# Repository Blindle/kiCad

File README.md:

# kiCad
electronic circuit - schema

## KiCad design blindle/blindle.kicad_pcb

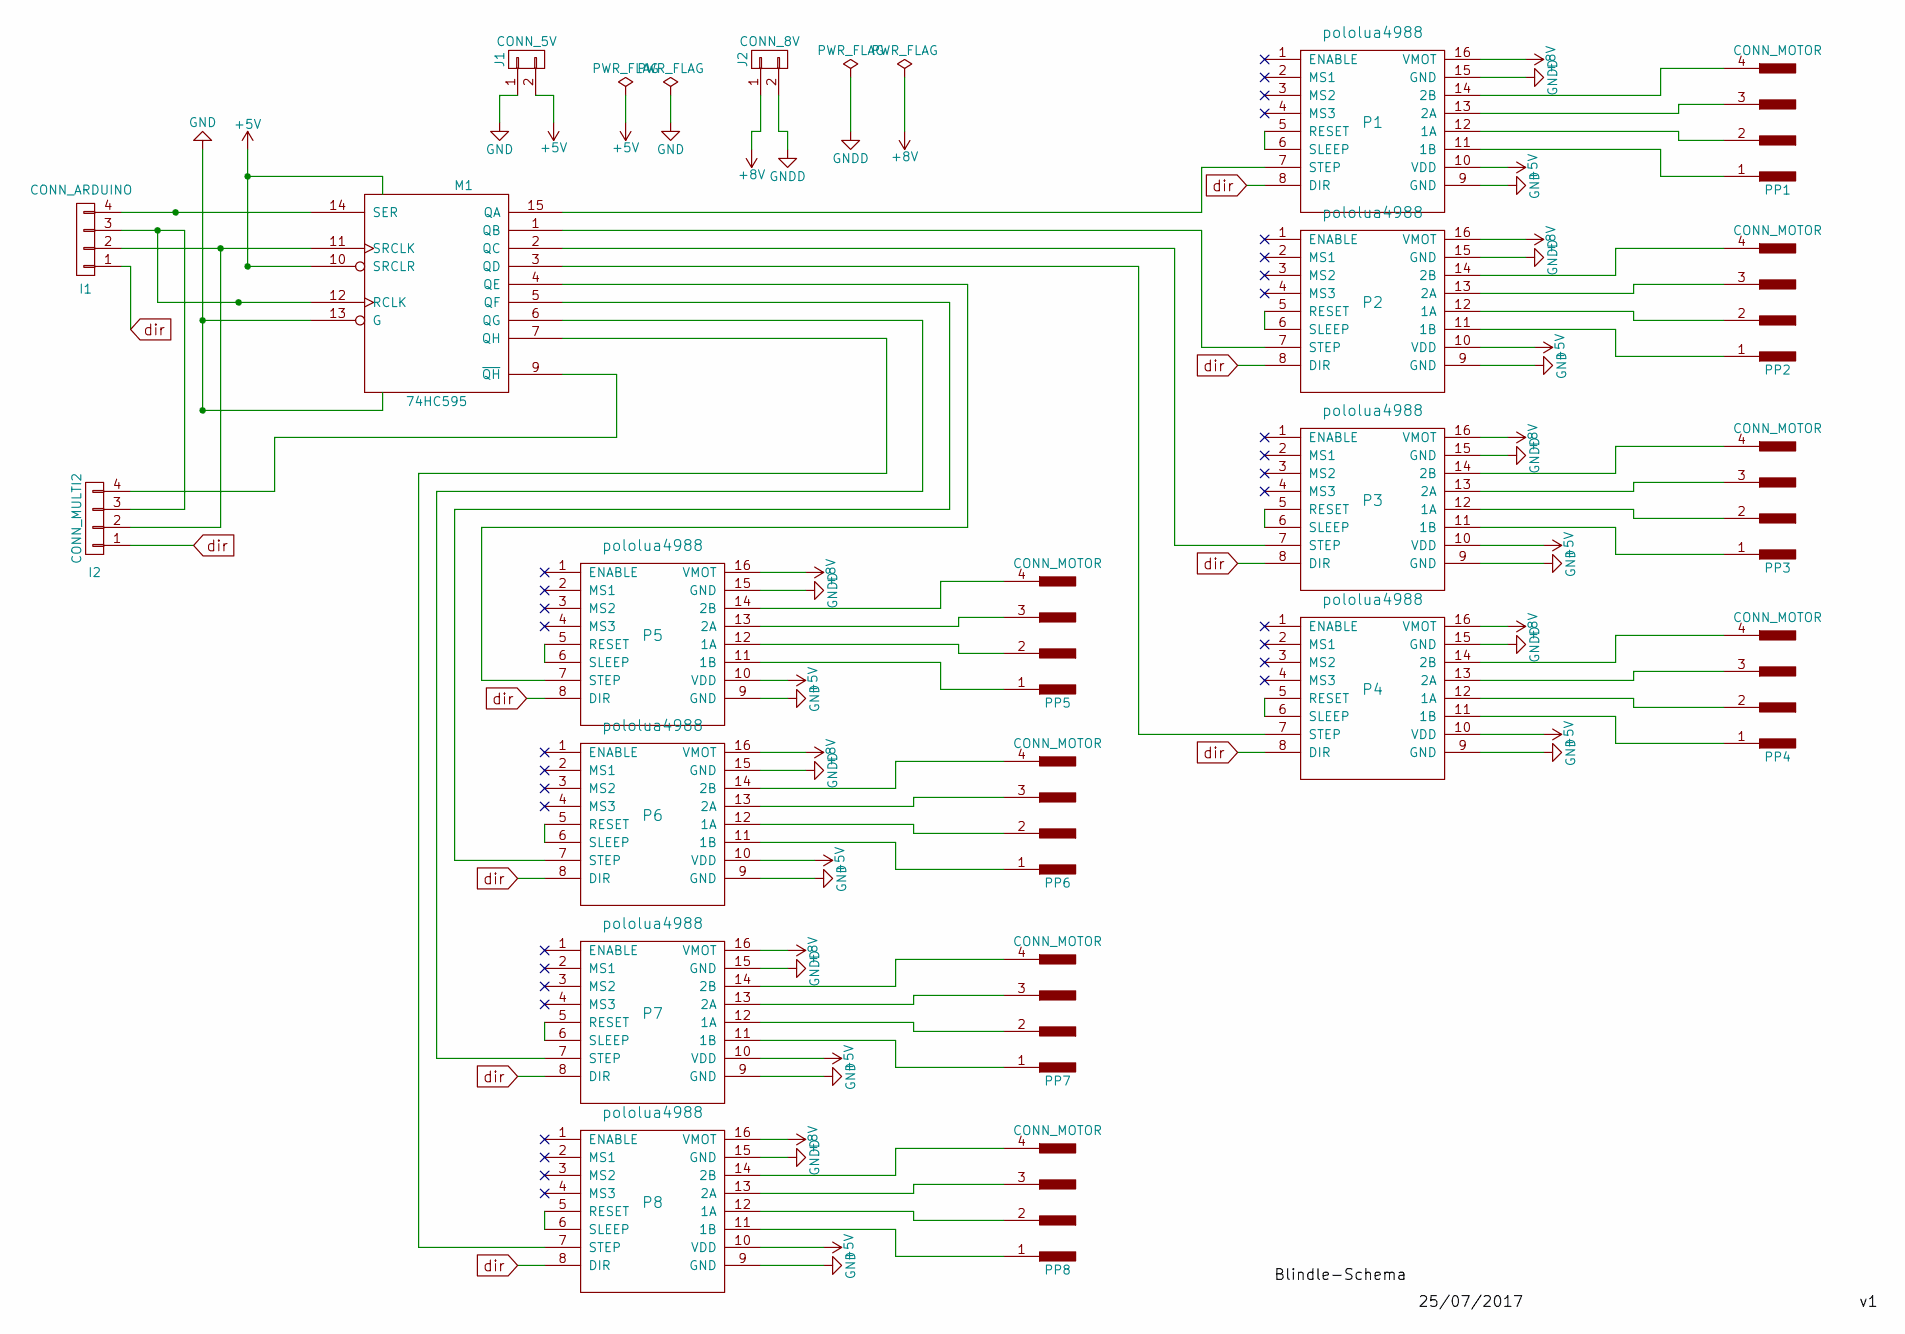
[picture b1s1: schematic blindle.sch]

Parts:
I1: CONN_ARDUINO; Pin_Header_Straight_1x04_Pitch2.54mm
I2: CONN_MULTI2; Pin_Header_Straight_1x04_Pitch2.54mm
J1: CONN_5V; PINHEAD1-2
J2: CONN_8V; bornier2
M1: 74HC595; DIP-16_W7.62mm_LongPads
P1, P2, P3, P4, P5, P6, P7, P8: pololua4988
PP1, PP2, PP3, PP4, PP5, PP6, PP7, PP8: CONN_MOTOR; Pin_Header_Straight_1x04_Pitch2.54mm

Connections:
+5V: J1.2, M1.10 (SRCLR), M1.16 (VCC), P1.10 (VDD), P2.10 (VDD), P3.10 (VDD), P4.10 (VDD), P5.10 (VDD), P6.10 (VDD), P7.10 (VDD), P8.10 (VDD)
+8V: J2.1, P1.16 (VMOT), P2.16 (VMOT), P3.16 (VMOT), P4.16 (VMOT), P5.16 (VMOT), P6.16 (VMOT), P7.16 (VMOT), P8.16 (VMOT)
GND: J1.1, M1.8 (GND), M1.13 (G), P1.9 (GND), P2.9 (GND), P3.9 (GND), P4.9 (GND), P5.9 (GND), P6.9 (GND), P7.9 (GND), P8.9 (GND)
GNDD: J2.2, P1.15 (GND), P2.15 (GND), P3.15 (GND), P4.15 (GND), P5.15 (GND), P6.15 (GND), P7.15 (GND), P8.15 (GND)
unnamed: I1.2, I2.2, M1.11 (SRCLK)
unnamed: I1.3, I2.3, M1.12 (RCLK)
unnamed: I1.4, M1.14 (SER)
unnamed: I2.4, M1.9 (~QH)
unnamed: M1.1 (QB), P2.7 (STEP)
unnamed: M1.2 (QC), P3.7 (STEP)
unnamed: M1.3 (QD), P4.7 (STEP)
unnamed: M1.4 (QE), P5.7 (STEP)
unnamed: M1.5 (QF), P6.7 (STEP)
unnamed: M1.6 (QG), P7.7 (STEP)
unnamed: M1.7 (QH), P8.7 (STEP)
unnamed: M1.15 (QA), P1.7 (STEP)
unnamed: P1.5 (RESET), P1.6 (SLEEP)
unnamed: P1.11 (1B), PP1.1
unnamed: P1.12 (1A), PP1.2
unnamed: P1.13 (2A), PP1.3
unnamed: P1.14 (2B), PP1.4
unnamed: P2.5 (RESET), P2.6 (SLEEP)
unnamed: P2.11 (1B), PP2.1
unnamed: P2.12 (1A), PP2.2
unnamed: P2.13 (2A), PP2.3
unnamed: P2.14 (2B), PP2.4
unnamed: P3.5 (RESET), P3.6 (SLEEP)
unnamed: P3.11 (1B), PP3.1
unnamed: P3.12 (1A), PP3.2
unnamed: P3.13 (2A), PP3.3
unnamed: P3.14 (2B), PP3.4
unnamed: P4.5 (RESET), P4.6 (SLEEP)
unnamed: P4.11 (1B), PP4.1
unnamed: P4.12 (1A), PP4.2
unnamed: P4.13 (2A), PP4.3
unnamed: P4.14 (2B), PP4.4
unnamed: P5.5 (RESET), P5.6 (SLEEP)
unnamed: P5.11 (1B), PP5.1
unnamed: P5.12 (1A), PP5.2
unnamed: P5.13 (2A), PP5.3
unnamed: P5.14 (2B), PP5.4
unnamed: P6.5 (RESET), P6.6 (SLEEP)
unnamed: P6.11 (1B), PP6.1
unnamed: P6.12 (1A), PP6.2
unnamed: P6.13 (2A), PP6.3
unnamed: P6.14 (2B), PP6.4
unnamed: P7.5 (RESET), P7.6 (SLEEP)
unnamed: P7.11 (1B), PP7.1
unnamed: P7.12 (1A), PP7.2
unnamed: P7.13 (2A), PP7.3
unnamed: P7.14 (2B), PP7.4
unnamed: P8.5 (RESET), P8.6 (SLEEP)
unnamed: P8.11 (1B), PP8.1
unnamed: P8.12 (1A), PP8.2
unnamed: P8.13 (2A), PP8.3
unnamed: P8.14 (2B), PP8.4
dir: I1.1, I2.1, P1.8 (DIR), P2.8 (DIR), P3.8 (DIR), P4.8 (DIR), P5.8 (DIR), P6.8 (DIR), P7.8 (DIR), P8.8 (DIR)

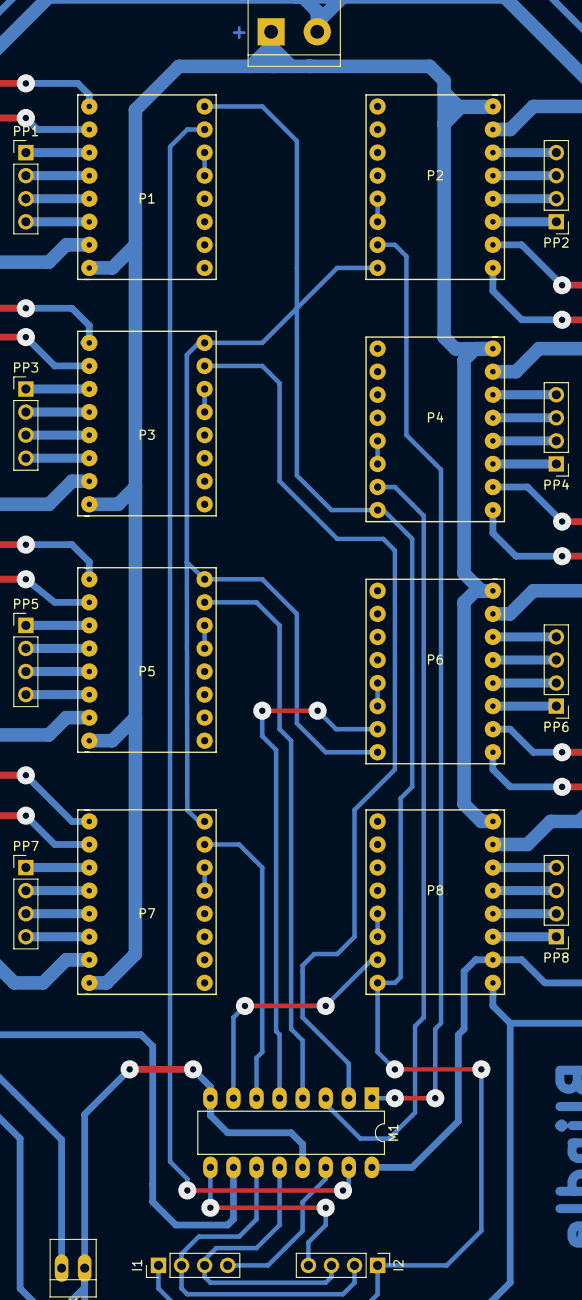
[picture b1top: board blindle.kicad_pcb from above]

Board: 2 copper layers, 21 parts (0 on the bottom side), 57 nets.

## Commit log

2017-07-24 Actualizo la huella del pololu
2017-07-24 Bug en plantilla pololu - Version 4 pololus
2017-07-24 8 pololu - En desarrollo
2017-07-27 pololu 8 - final v1 pcb
2017-08-01 Refinamiento de diseño pcb y footprint pololu
2017-08-01 version de placa final
2017-08-06 version para placa mas chica
2017-08-07 cambios menores
2017-11-07 pcb.pdf
